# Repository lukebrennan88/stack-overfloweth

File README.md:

# stack-overfloweth
purdue milestones stuff

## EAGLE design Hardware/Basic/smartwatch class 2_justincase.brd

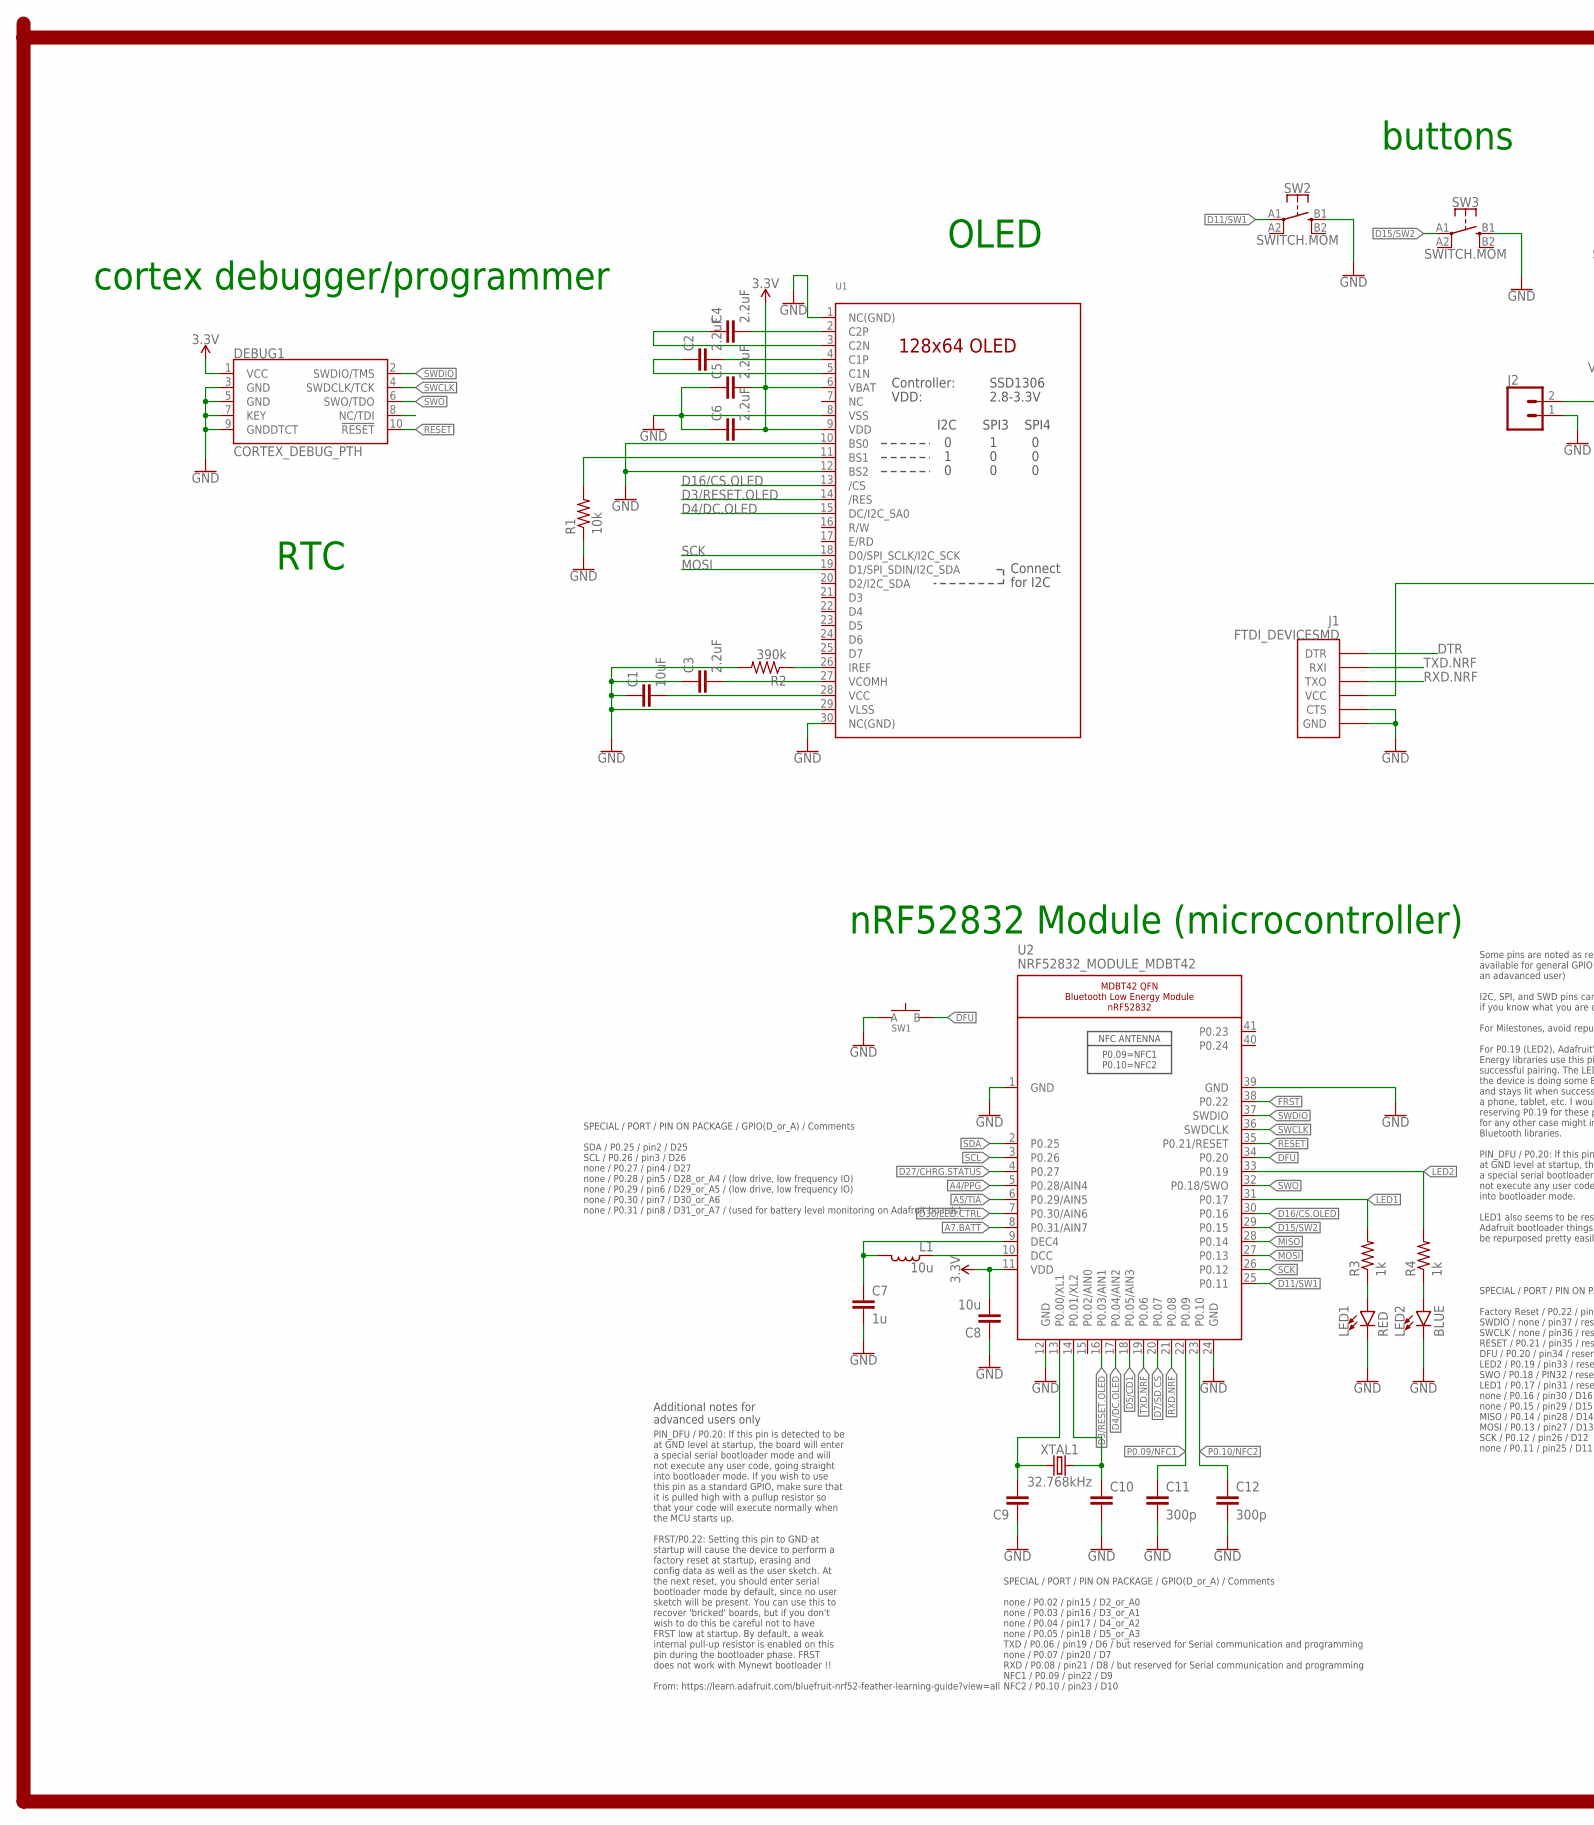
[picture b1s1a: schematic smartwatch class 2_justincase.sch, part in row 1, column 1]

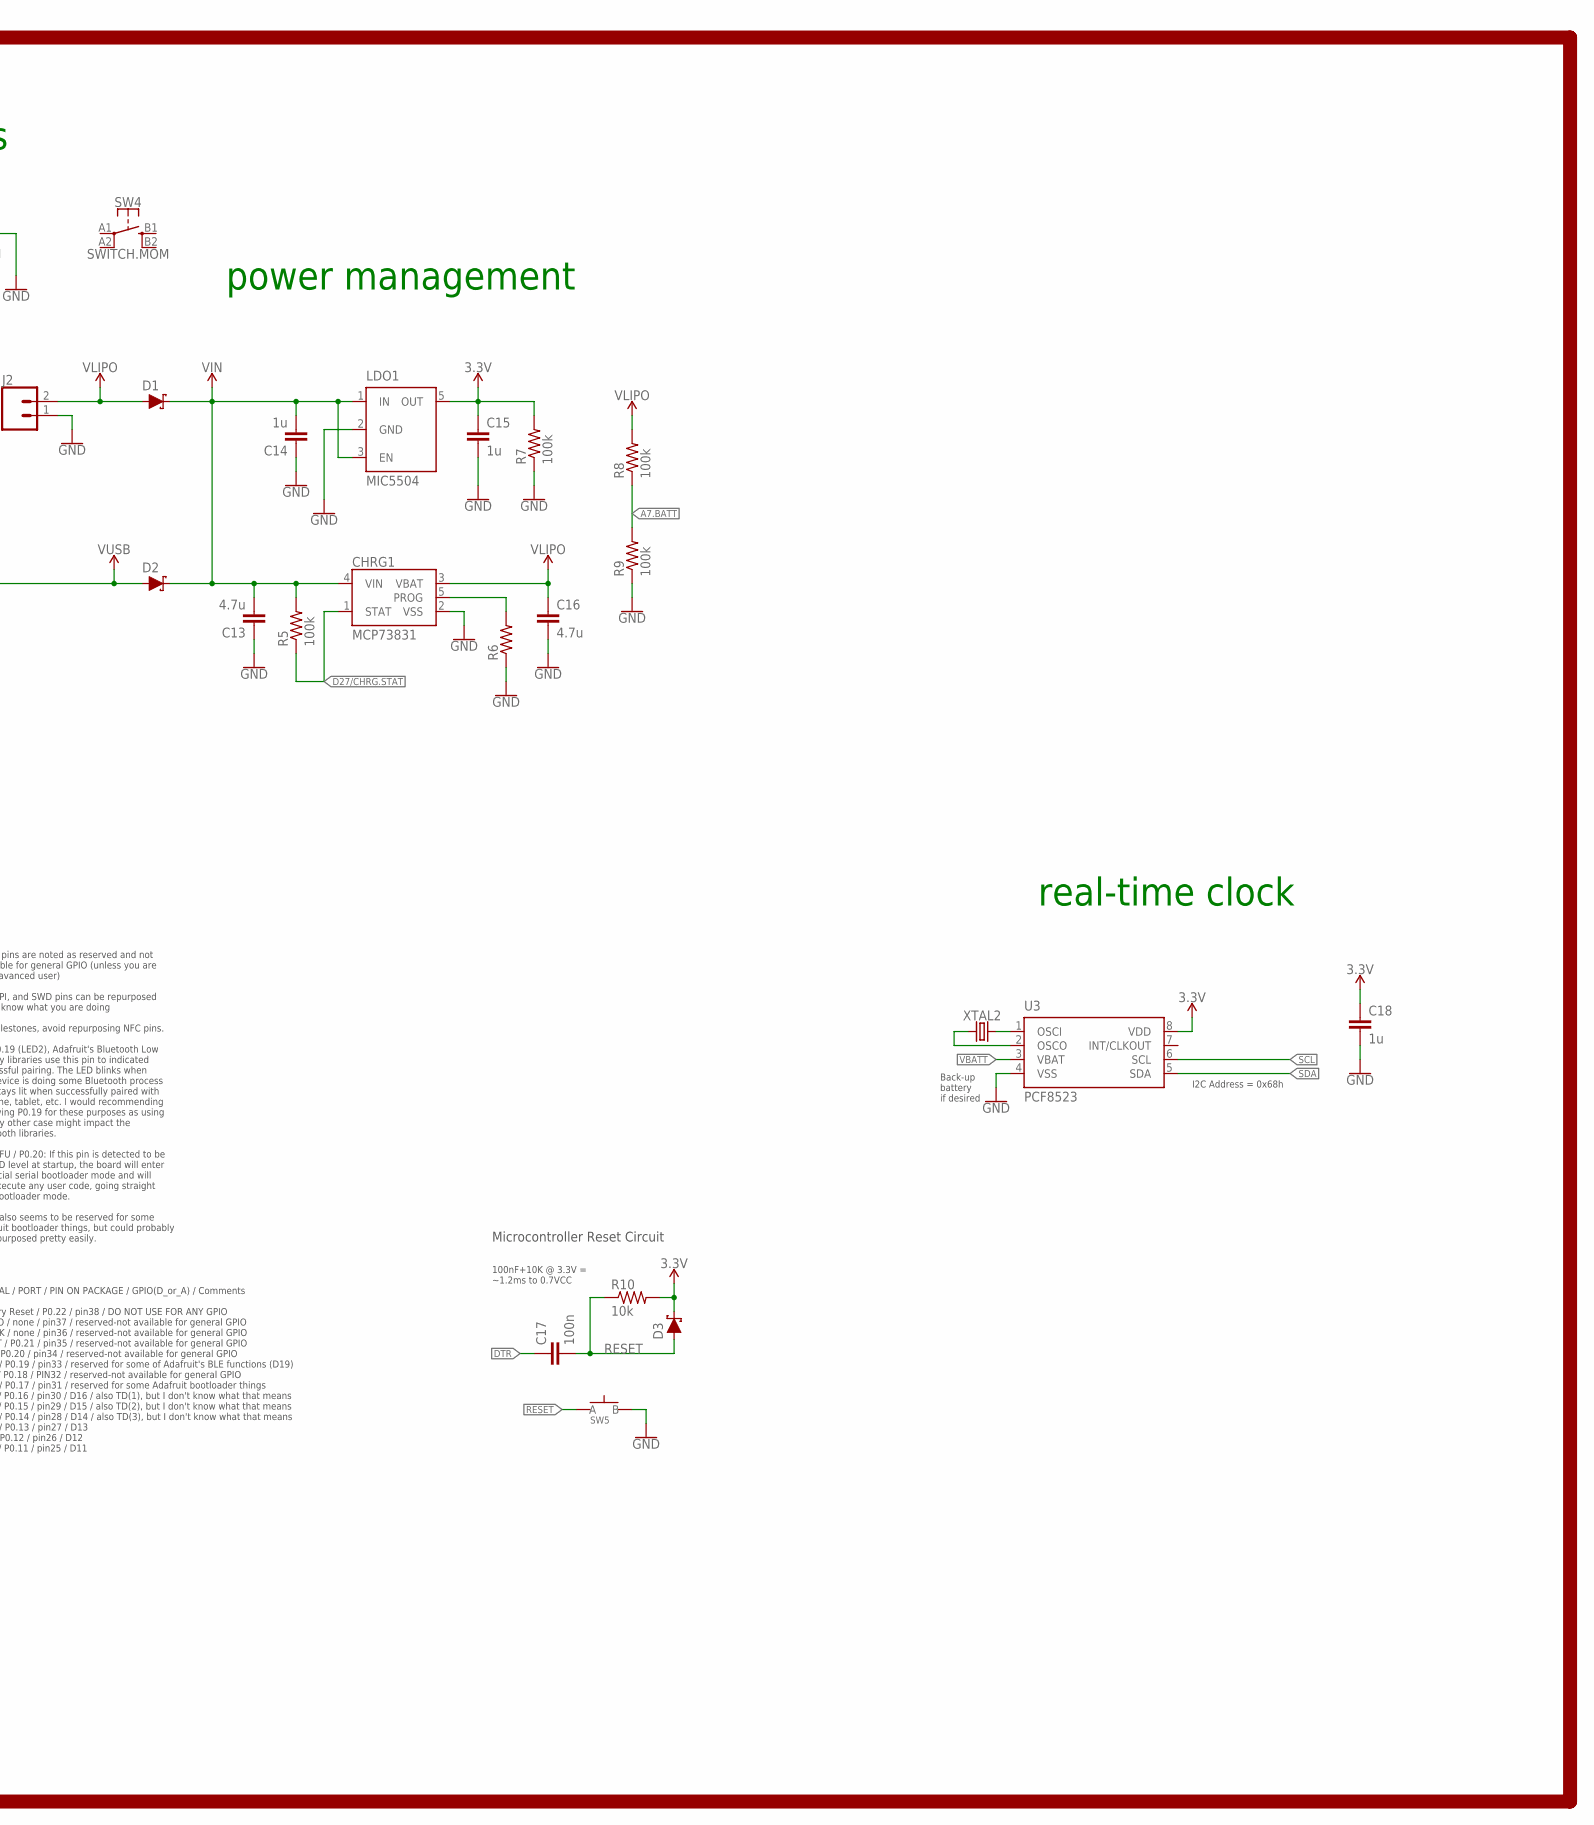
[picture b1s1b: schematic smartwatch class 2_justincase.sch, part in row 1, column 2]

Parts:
C1: 10uF; C0603
C2, C3, C4, C5, C6: 2.2uF; C0603
C7, C14, C15, C18: 1u; C0603
C8: 10u; C0805
C9, C10: CAPACITOR0603; C0603
C11, C12: 300p; C0603
C13, C16: 4.7u; C0603
C17: 100n; C0603
CHRG1: MCP73831; SOT23-5
D1, D2, D3: SCHOTTKY-USC; USC
DEBUG1: CORTEX_DEBUG_PTH; 2X5-PTH-1.27MM
J1: FTDI_DEVICESMD; FTDI-SMD
J2: CONN_02; 1X02
L1: 10u; L0603
LDO1: MIC5504; SOT23-5
LED1: RED; LED-0603
LED2: BLUE; LED-0603
R1, R10: 10k; R0603
R2: 390k; R0603
R3, R4: 1k; R0603
R5, R7, R8, R9: 100k; R0603
R6: RESISTOR0603; R0603
SW1, SW5: SPST-PTS830GG140-COPY.1-3; BUTTON-GULLWING
SW2, SW3, SW4: SWITCH.MOM; TACTILE_SWITCH_SMD_6.2MM_TALL
U1: DISP_OLED_UG-2864HSWEG01-NO-WRAPAROUND; UG-2864HSWEG01_0.96IN_NO-WRAPAROUND
U2: NRF52832_MODULE_MDBT42; BLE_MODULE_RAYTAC_MDBT42
U3: PCF8523; SO8; DIGIKEY 568-5306-1-ND
XTAL1: 32.768kHz; 2-SMD.NOLEAD.2.0MMTO1.2MM
XTAL2: 32.7680kHz; 2-SMD.NOLEAD.2.0MMTO1.2MM

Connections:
3.3V: C5.2, C6.2, C8.2, C15.1, C18.1, D3.- (C), DEBUG1.1 (VCC), LDO1.5 (OUT), R7.2, R10.2, U1.6 (VBAT), U1.9 (VDD), U2.11 (VDD), U3.8 (VDD)
A4/PPG: U2.5 (P0.28/AIN4)
A5/TIA: U2.6 (P0.29/AIN5)
A7.BATT: R8.1, R9.2, U2.8 (P0.31/AIN7)
D3/RESET.OLED: U1.14 (/RES), U2.16 (P0.03/AIN1)
D4/DC.OLED: U1.15 (DC/I2C_SA0), U2.17 (P0.04/AIN2)
D5/CD1: U2.18 (P0.05/AIN3)
D7/SD.CS: U2.20 (P0.07)
D11/SW1: SW2.A1 (1), U2.25 (P0.11)
D15/SW2: SW3.A1 (1), U2.29 (P0.15)
D16/CS.OLED: U1.13 (/CS), U2.30 (P0.16)
D27/CHRG.STAT: CHRG1.1 (STAT), R5.1
D27/CHRG.STATUS: U2.4 (P0.27)
D30/LED.CTRL: U2.7 (P0.30/AIN6)
DFU: SW1.3 (B), U2.34 (P0.20)
DTR: C17.1, J1.DTR
FRST: U2.38 (P0.22)
GND: C1.1, C3.1, C5.1, C6.1, C7.2, C8.1, C9.1, C10.2, C11.2, C12.2, C13.1, C14.1, C15.2, C16.2, C18.2, CHRG1.2 (VSS), DEBUG1.3 (GND), DEBUG1.5 (GND), DEBUG1.7 (KEY), DEBUG1.9 (GNDDTCT), J1.CTS, J1.GND, J2.1, LDO1.2 (GND), LED1.C, LED2.C, R1.1, R2.2, R6.1, R7.1, R9.1, SW1.1 (A), SW2.B1 (3), SW3.B1 (3), SW5.3 (B), U1.1 (NC(GND)), U1.8 (VSS), U1.10 (BS0), U1.12 (BS2), U1.29 (VLSS), U1.30 (NC(GND)), U2.1 (GND), U2.12 (GND), U2.24 (GND), U2.39 (GND), U3.4 (VSS)
LED1: R3.2, U2.31 (P0.17)
LED2: R4.2, U2.33 (P0.19)
MISO: U2.28 (P0.14)
MOSI: U1.19 (D1/SPI_SDIN/I2C_SDA), U2.27 (P0.13)
unnamed: C9.2, U2.13 (P0.00/XL1), XTAL1.P$1 (1)
unnamed: C10.1, U2.14 (P0.01/XL2), XTAL1.P$2 (2)
unnamed: L1.1, U2.10 (DCC)
unnamed: R1.2, U1.11 (BS1)
unnamed: LED1.A, R3.1
unnamed: R2.1, U1.26 (IREF)
unnamed: LED2.A, R4.1
unnamed: C7.1, L1.2, U2.9 (DEC4)
unnamed: C4.2, U1.2 (C2P)
unnamed: C4.1, U1.3 (C2N)
unnamed: C2.2, U1.4 (C1P)
unnamed: C2.1, U1.5 (C1N)
unnamed: C1.2, U1.28 (VCC)
unnamed: C3.2, U1.27 (VCOMH)
unnamed: CHRG1.5 (PROG), R6.2
unnamed: U3.2 (OSCO), XTAL2.P$1 (1)
unnamed: U3.1 (OSCI), XTAL2.P$2 (2)
P0.09/NFC1: C11.1, U2.22 (P0.09)
P0.10/NFC2: C12.1, U2.23 (P0.10)
RESET: C17.2, D3.+ (A), DEBUG1.10 (!RESET), R10.1, SW5.1 (A), U2.35 (P0.21/RESET)
RXD.NRF: J1.TXO, U2.21 (P0.08)
SCK: U1.18 (D0/SPI_SCLK/I2C_SCK), U2.26 (P0.12)
SCL: U2.3 (P0.26), U3.6 (SCL)
SDA: U2.2 (P0.25), U3.5 (SDA)
SWCLK: DEBUG1.4 (SWDCLK/TCK), U2.36 (SWDCLK)
SWDIO: DEBUG1.2 (SWDIO/TMS), U2.37 (SWDIO)
SWO: DEBUG1.6 (SWO/TDO), U2.32 (P0.18/SWO)
TXD.NRF: J1.RXI, U2.19 (P0.06)
VBATT: U3.3 (VBAT)
VIN: C13.2, C14.2, CHRG1.4 (VIN), D1.- (C), D2.- (C), LDO1.1 (IN), LDO1.3 (EN), R5.2
VLIPO: C16.1, CHRG1.3 (VBAT), D1.+ (A), J2.2, R8.2
V_USB: D2.+ (A), J1.VCC

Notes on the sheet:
Microcontroller Reset Circuit
100nF+10K @ 3.3V = ~1.2ms to 0.7VCC
SPECIAL / PORT / PIN ON PACKAGE / GPIO(D_or_A) / Comments SDA / P0.25 / pin2 / D25 SCL / P0.26 / pin3 / D26 none / P0.27 / pin4 / D27 none / P0.28 / pin5 / D28_or_A4 / (low drive, low frequency IO) none / P0.29 / pin6 / D29_or_A5 / (low drive, low frequency IO) none / P0.30 / pin7 / D30_or_A6 none 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
SPECIAL / PORT / PIN ON PACKAGE / GPIO(D_or_A) / Comments none / P0.02 / pin15 / D2_or_A0 none / P0.03 / pin16 / D3_or_A1 none / P0.04 / pin17 / D4_or_A2 none / P0.05 / pin18 / D5_or_A3 TXD / P0.06 / pin19 / D6 / but reserved for Serial communication and programming none / P0.07 / pin20 / D7 RXD / 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
SPECIAL / PORT / PIN ON PACKAGE / GPIO(D_or_A) / Comments Factory Reset / P0.22 / pin38 / DO NOT USE FOR ANY GPIO SWDIO / none / pin37 / reserved-not available for general GPIO SWCLK / none / pin36 / reserved-not available for general GPIO RESET / P0.21 / pin35 / reserved-not available for general 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
Some pins are noted as reserved and not available for general GPIO (unless you are an adavanced user) I2C, SPI, and SWD pins can be repurposed if you know what you are doing For Milestones, avoid repurposing NFC pins. For P0.19 (LED2), Adafruit's Bluetooth Low Energy libraries use this pin to indic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
PIN_DFU / P0.20: If this pin is detected to be at GND level at startup, the board will enter a special serial bootloader mode and will not execute any user code, going straight into bootloader mode. If you wish to use this pin as a standard GPIO, make sure that it is pulled high with a pullup resis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
Additional notes for advanced users only
I2C Address = 0x68h
Back-up battery if desired
nRF52832 Module (microcontroller)
OLED
power management
buttons
real-time clock
cortex debugger/programmer
RTC

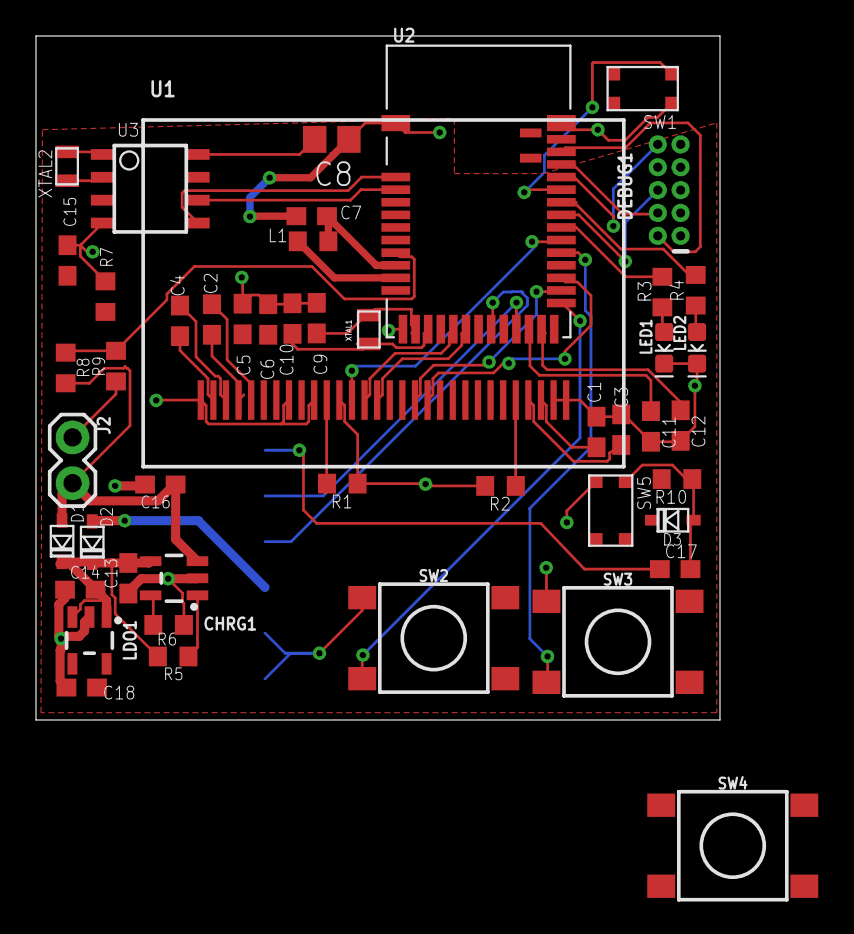
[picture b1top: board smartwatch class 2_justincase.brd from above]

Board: 2 copper layers, 38.0 x 38.0 mm, 49 parts (1 on the bottom side), 45 nets.

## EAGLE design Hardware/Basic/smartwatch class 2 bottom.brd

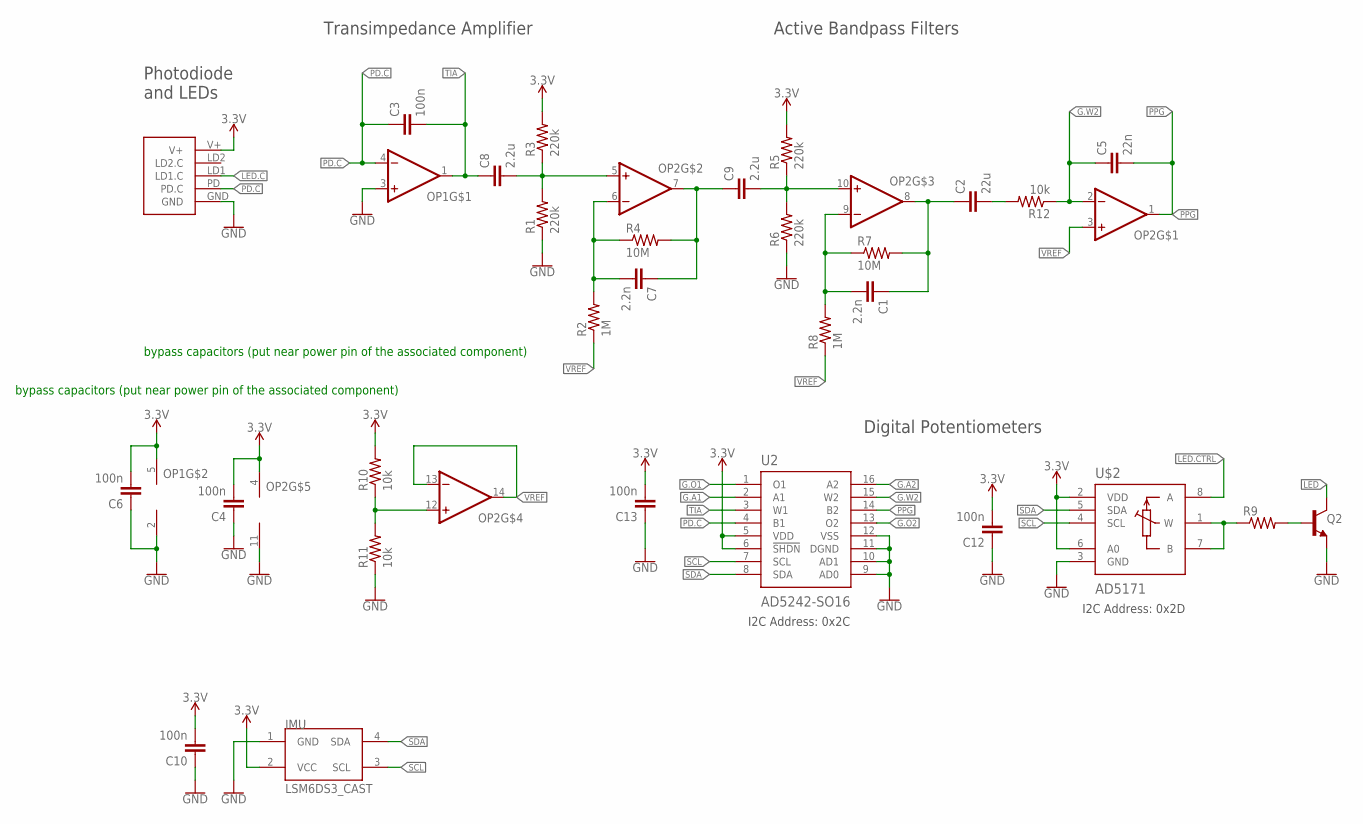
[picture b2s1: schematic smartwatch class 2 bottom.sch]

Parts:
C1, C7: 2.2n; C0603
C2: 22u; C0603
C3, C4, C6, C10, C12, C13: 100n; C0603
C5: 22n; C0603
C8, C9: 2.2u; C0603
IMU: LSM6DS3_CAST
OP1: OP-SINGLEOT; SOT23-5
OP2: OP-QUAD-SO14; SO14
Q2: NPN-GENERIC; SOT23-3
R1, R3, R5, R6: 220k; R0603
R2, R8: 1M; R0603
R4, R7: 10M; R0603
R9: RESISTOR0603; R0603
R10, R11: 10k; R0402
R12: 10k; R0603
U2: AD5242-SO16; SO16
U$1: PPG.MODULE.2
U$2: AD5171; SOT-23-8

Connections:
3.3V: C4.2, C6.2, C10.2, C12.2, C13.2, IMU.2 (VCC), OP1.5 (V+), OP2.4 (V+), R3.2, R5.2, R10.2, U2.5 (VDD), U2.6 (!SHDN), U$1.V+, U$2.2 (VDD), U$2.6 (A0)
G.A1: U2.2 (A1)
G.A2: U2.16 (A2)
G.O1: U2.1 (O1)
G.O2: U2.13 (O2)
G.W2: C5.1, OP2.2 (-IN), R12.1, U2.15 (W2)
GND: C4.1, C6.1, C10.1, C12.1, C13.1, IMU.1 (GND), OP1.2 (V-), OP1.3 (+IN), OP2.11 (V-), Q2.2 (E), R1.1, R6.1, R11.1, U2.9 (AD0), U2.10 (AD1), U2.11 (DGND), U2.12 (VSS), U$1.GND, U$2.3 (GND)
LED: Q2.3 (C)
LED.C: U$1.LD1 (LD1.C)
LED.CTRL: U$2.8 (A)
unnamed: C8.2, OP2.5 (+IN), R1.2, R3.1
unnamed: C9.2, OP2.10 (+IN), R5.1, R6.2
unnamed: C7.2, OP2.6 (-IN), R2.2, R4.1
unnamed: C7.1, C9.1, OP2.7 (OUT), R4.2
unnamed: C1.2, OP2.9 (-IN), R7.1, R8.2
unnamed: C1.1, C2.1, OP2.8 (OUT), R7.2
unnamed: C2.2, R12.2
unnamed: Q2.1 (B), R9.2
unnamed: R9.1, U$2.1 (W), U$2.7 (B)
unnamed: OP2.12 (+IN), R10.1, R11.2
PD.C: C3.1, OP1.4 (-IN), U2.4 (B1), U$1.PD (PD.C)
PPG: C5.2, OP2.1 (OUT), U2.14 (B2)
SCL: IMU.3 (SCL), U2.7 (SCL), U$2.4 (SCL)
SDA: IMU.4 (SDA), U2.8 (SDA), U$2.5 (SDA)
TIA: C3.2, C8.1, OP1.1 (OUT), U2.3 (W1)
VREF: OP2.3 (+IN), OP2.13 (-IN), OP2.14 (OUT), R2.1, R8.1

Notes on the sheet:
Photodiode and LEDs
Active Bandpass Filters
Digital Potentiometers
Transimpedance Amplifier
I2C Address: 0x2C
I2C Address: 0x2D
bypass capacitors (put near power pin of the associated component)

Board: 2 copper layers, 31 parts (0 on the bottom side), 19 nets, no tracks yet.

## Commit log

2022-09-08 Create .gitignore
    make a .gitignore file for files we don't want git to see in the repository
2022-09-08 blank eagle and arduino files
2022-09-15 class 2 progress
2022-09-17 finished class 2 video
2022-09-22 class three stuff, the arduino code doesn't compile and it is still on the arduino board as opposed to the n###### feather board which orlando did in the example
2022-10-05 deleted the second board and partially wired the board
2022-10-06 at 14:14 of video 2
2022-11-02 video 2 35:46 but may be all wired up anyway
2022-11-03 just hooked up the A7.batt
